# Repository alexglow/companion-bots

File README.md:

# companion-bots
Stuff about companion bots – see the [wiki](https://github.com/alexglow/companion-bots/wiki)!

## F3NR1R scripts
Python and Arduino scripts used in F3NR1R, my fennec-inspired shoulder AI bot.

## Companion Core  
// project: https://www.hackster.io/glowascii/companion-core-robot-heart-c79f52  
// order: https://oshpark.com/shared_projects/OIsucXlD  
KiCad PCB design files for my "Companion Core" board. It connects a Teensy or Arduino Nano 33 BLE Sense to servos, NeoPixels, etc., and powers the peripherals.  
Until I get a chance to clean up the directory, it's a mess! Use the -spine versions.  
May contain some custom footprints that I need to chase down and bundle up. 

## Purr Module  
// project: https://www.hackster.io/glowascii/purr-module-for-companion-bots-fe393d  
// order: https://oshpark.com/shared_projects/xRD2UXla  
KiCad PCB design files for v1 of the Purr Module. It allows you to connect one or two pairs of haptic vibration motors to a 5V source (e.g., USB power pack). Next version will have a transistor built in and a 3-pin connector for the Companion Core, just like a servo or WS2812 LEDs!

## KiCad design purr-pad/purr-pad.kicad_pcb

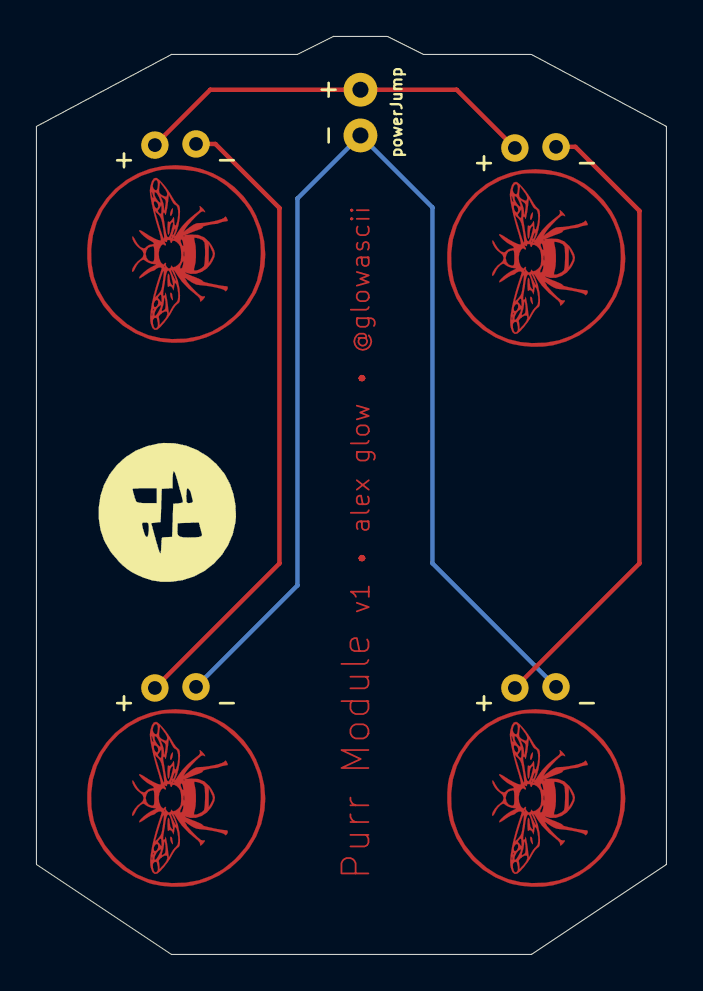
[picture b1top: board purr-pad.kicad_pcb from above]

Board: 2 copper layers, 35.0 x 51.0 mm, 6 parts (0 on the bottom side), 4 nets.

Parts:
 : hlogoTiny
 #2: powerJump; 2-pin-power
M1, M2, M3, M4: MOTOR10MM; bee-vibe-cu

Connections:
unnamed: #2.1, M1.+, M3.+
unnamed: #2.2, M2.-, M4.-
unnamed: M1.-, M2.+
unnamed: M3.-, M4.+

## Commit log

2021-04-23 Add F3NR1R files
    Add audio files and Python scripts for F3NR1R fennec companion bot (bit.ly/f3nr1r).
2021-10-28 Adding Companion Core
2021-12-06 add purr module
